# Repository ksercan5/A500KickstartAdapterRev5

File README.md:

# A500KiclstartAdapterRev5
Amiga 500 Kickstart Adapter for Rev5 boards

Use this board to use burned EPROMs for your Amiga 500 computer with Rev5 board

You can use 27c400 or 27C800 EPROMs, If you use 27C400 EPROM leave top 2 pins empty, 

You can also make use of 2 kickstart images if you use 27800 EPROM, you can use a switch or a jumper to select kickstart. Also you can put a long cable to extend the switch out ofthe case

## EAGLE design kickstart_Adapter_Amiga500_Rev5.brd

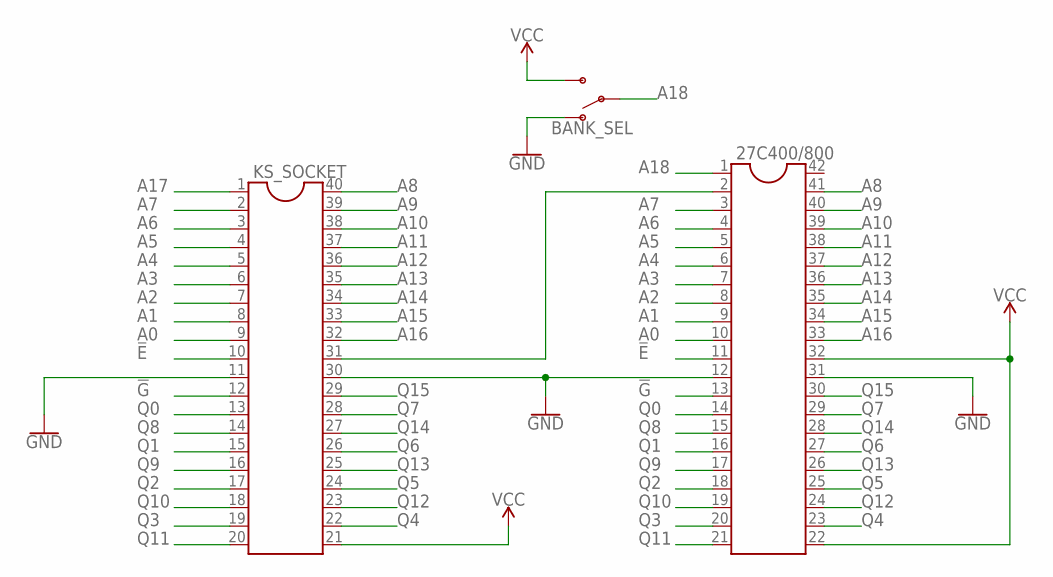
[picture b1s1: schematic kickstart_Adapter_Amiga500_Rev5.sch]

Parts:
27C400/800: DIL42
BANK_SEL: SWITCH-SPDT-PTH-11.6X4.0MM; SWITCH_SPDT_PTH_11.6X4.0MM
KS_SOCKET: DIL40

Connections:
!E: 27C400/800.11, KS_SOCKET.10
!G: 27C400/800.13, KS_SOCKET.12
A0: 27C400/800.10, KS_SOCKET.9
A1: 27C400/800.9, KS_SOCKET.8
A2: 27C400/800.8, KS_SOCKET.7
A3: 27C400/800.7, KS_SOCKET.6
A4: 27C400/800.6, KS_SOCKET.5
A5: 27C400/800.5, KS_SOCKET.4
A6: 27C400/800.4, KS_SOCKET.3
A7: 27C400/800.3, KS_SOCKET.2
A8: 27C400/800.41, KS_SOCKET.40
A9: 27C400/800.40, KS_SOCKET.39
A10: 27C400/800.39, KS_SOCKET.38
A11: 27C400/800.38, KS_SOCKET.37
A12: 27C400/800.37, KS_SOCKET.36
A13: 27C400/800.36, KS_SOCKET.35
A14: 27C400/800.35, KS_SOCKET.34
A15: 27C400/800.34, KS_SOCKET.33
A16: 27C400/800.33, KS_SOCKET.32
A17: 27C400/800.2, KS_SOCKET.1, KS_SOCKET.31
A18: 27C400/800.1, BANK_SEL.2
GND: 27C400/800.12, 27C400/800.31, BANK_SEL.1 (O), KS_SOCKET.11, KS_SOCKET.30
Q0: 27C400/800.14, KS_SOCKET.13
Q1: 27C400/800.16, KS_SOCKET.15
Q2: 27C400/800.18, KS_SOCKET.17
Q3: 27C400/800.20, KS_SOCKET.19
Q4: 27C400/800.23, KS_SOCKET.22
Q5: 27C400/800.25, KS_SOCKET.24
Q6: 27C400/800.27, KS_SOCKET.26
Q7: 27C400/800.29, KS_SOCKET.28
Q8: 27C400/800.15, KS_SOCKET.14
Q9: 27C400/800.17, KS_SOCKET.16
Q10: 27C400/800.19, KS_SOCKET.18
Q11: 27C400/800.21, KS_SOCKET.20
Q12: 27C400/800.24, KS_SOCKET.23
Q13: 27C400/800.26, KS_SOCKET.25
Q14: 27C400/800.28, KS_SOCKET.27
Q15: 27C400/800.30, KS_SOCKET.29
VCC: 27C400/800.22, 27C400/800.32, BANK_SEL.3 (S), KS_SOCKET.21

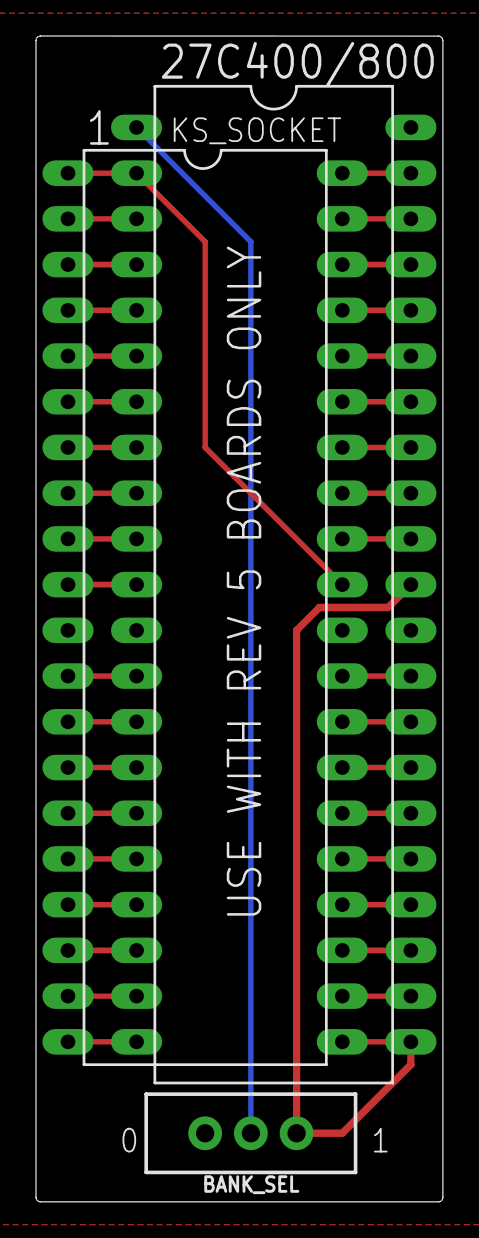
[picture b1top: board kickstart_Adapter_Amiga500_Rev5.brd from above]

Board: 2 copper layers, 22.6 x 64.8 mm, 3 parts (0 on the bottom side), 39 nets.

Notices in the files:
parts and their libraries:
SparkFun-Switches: Licensing: Creative Commons ShareAlike 4.0 International - https://creativecommons.org/licenses/by-sa/4.0
